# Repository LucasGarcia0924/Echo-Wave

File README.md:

# Echo-Wave

Banner 

## Descripción 
Dispositivo capaz de clonar señales RF de 433mhz, siendo controlado desde una App Movil

Proyecto final asignatura de Taller de Electrónica 2024-1

Universidad Nacional de Colombia
### Integrantes
* Lucas Garcia Alvarez
* Julian Gustin Moreno
* Kevin Castellanos Peña
* Santiago Navarro

## Introducción
El proyecto EchoWave se creó con la idea de facilitar la clonación de señales RF de controles remotos de distintos tipos, utilizando materiales de bajo costo para crear un dispositivo capaz de replicar y usar dichas señales. 

## La problemática
En la actualidad, el uso de controles remotos para dispositivos que emiten señales RF, como televisores, luces y otros equipos, se ha vuelto parte de las actividades cotidianas. Sin embargo, los usuarios enfrentan varios inconvenientes:

- Limitaciones de compatibilidad: Muchas veces los usuarios necesitan múltiples controles remotos, cada uno con una función específica, lo que resulta incómodo y poco eficiente.
- Falta de flexibilidad: Las tecnologías existentes no permiten la clonación o replicación de señales de RF de manera sencilla, lo que genera frustración entre los usuarios que requieren soluciones rápidas y accesibles.
- Riesgos de seguridad: Clonar señales RF sin los adecuados controles de seguridad puede conllevar riesgos, lo que hace que los usuarios se sientan inseguros al intentar utilizar tecnologías más flexibles.
Estas problemáticas crean la necesidad de desarrollar soluciones más accesibles y económicas que permitan clonar y utilizar señales RF de manera segura y eficiente, facilitando así las acciones cotidianas de los usuarios.

El proyecto EchoWave busca solucionar esta problemática mediante la creación de un dispositivo de bajo costo, flexible y eficiente, que permita la clonación y uso de señales de RF de manera segura, mejorando la experiencia del usuario y reduciendo la cantidad de controles remotos necesarios para interactuar con múltiples dispositivos.
## La solución planteada (los módulos usados)
La solución se diseña a partir de tecnologías simples, de fácil acceso y fabricación, enfocados en parte a que sea algo accesible para todo el mundo, por lo que a partir de esto y demás requisitos descritos a continuacion, se eligen los siguientes componentes:
- Chip ESP32
- Batería Recargable IN18650
- Modulo MHCD 42
- Transceptor HC-12
- Servomotor SG90
- Zumbador
- Case en Impresion 3D y Corte Laser
## El funcionamiento del proyecto desde el punto de vista del usuario

El EchoWave funciona como un control remoto universal, que mediante una aplicación, clona señales RF, como las de un control de televisor, controles para puertas de garaje o portones, y otros dispositivos similares  
Su uso consta tan solo de descargar la aplicación, clonar señales, cargar el dispositivo mediante el cable incluido y bloquear las señales con el pulsador en la parte superior del case.

## Recomendaciones y conclusiones
### Conclusiones:
En este proyecto se logró avanzar en le creación de una herramienta capaz de simplificar las tarjetas de acceso y controles a distancia de forma compacta, sin embargo, se enfocó el proyecto a las señales de radiofrecuencia, donde por medio de un transceptor recibe estas señales. Dentro del proyecto se utilizaron componentes con presupuesto reducido, confirmando que en el mercado se consiguen dispositivos de bajo precio y con las características que permiten manejar las diferentes señales y comunicaciones que se implementan aquí. Se plantea en un futuro implementarle la opción de usarse a bluetooth y hacer el uso de este desde una app del celular, dado que, quitando al tranceptor el cual es controlado desde la app diseñada por Slavko Zdravevski se implementó un grupo de pulsadores sencillos para que inicie su funcionamiento, por lo que lo ideal sería integrar todos estos comandos dentro de la app y así eliminar los pulsadores de la PCB.

### Recomendaciones para trabajos futuros:
Visualizamos que puede ser muy útil, buscar diferentes antecedentes de proyectos similares, componentes capaces de llevar a cabo la tarea y evaluar cuál lenguaje de programación ha de usarse.
Si se quiere hacer un trabajo en grupo, debe existir muy buena comunicación, de forma continua y clara entre todos, para que no se se tengan retrasos en el proceso, facilitando la corrección de errores y permitiendo un continuo ciclo de ideas y retroalimentación, para que el proyecto fluya correctamente.
Se deben tener en cuenta los posibles obstáculos que se pueden presentar durante el proceso, como puede ser el mal funcionamiento de un componente, o el fallo del código; para ello es necesario saber que otras alternativas existen, para corregir el error que se produzca al realizar el proyecto.

## WIKI
Si desea conocer más sobre este proyecto, podrá encontrar toda la documentación en la sección de [wiki](https://github.com/LucasGarcia0924/Echo-Wave/wiki), además, en este apartado en la parte superior se encuentran adjuntos todos los archivos relacionados con el proyecto.

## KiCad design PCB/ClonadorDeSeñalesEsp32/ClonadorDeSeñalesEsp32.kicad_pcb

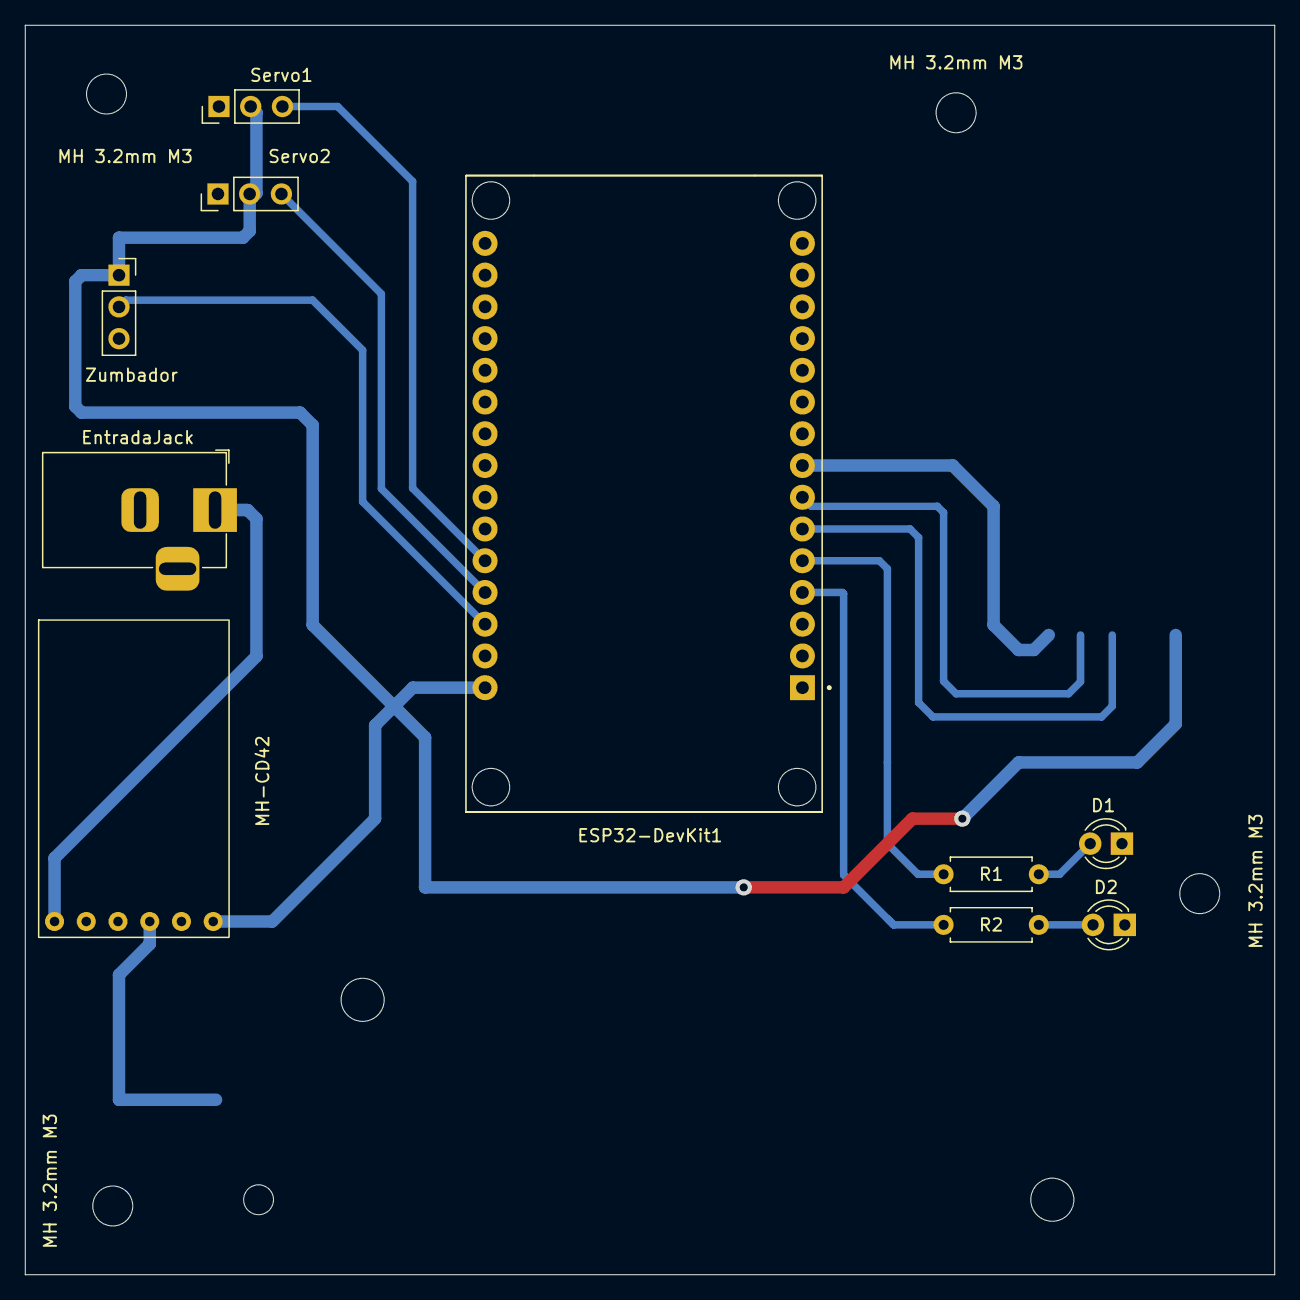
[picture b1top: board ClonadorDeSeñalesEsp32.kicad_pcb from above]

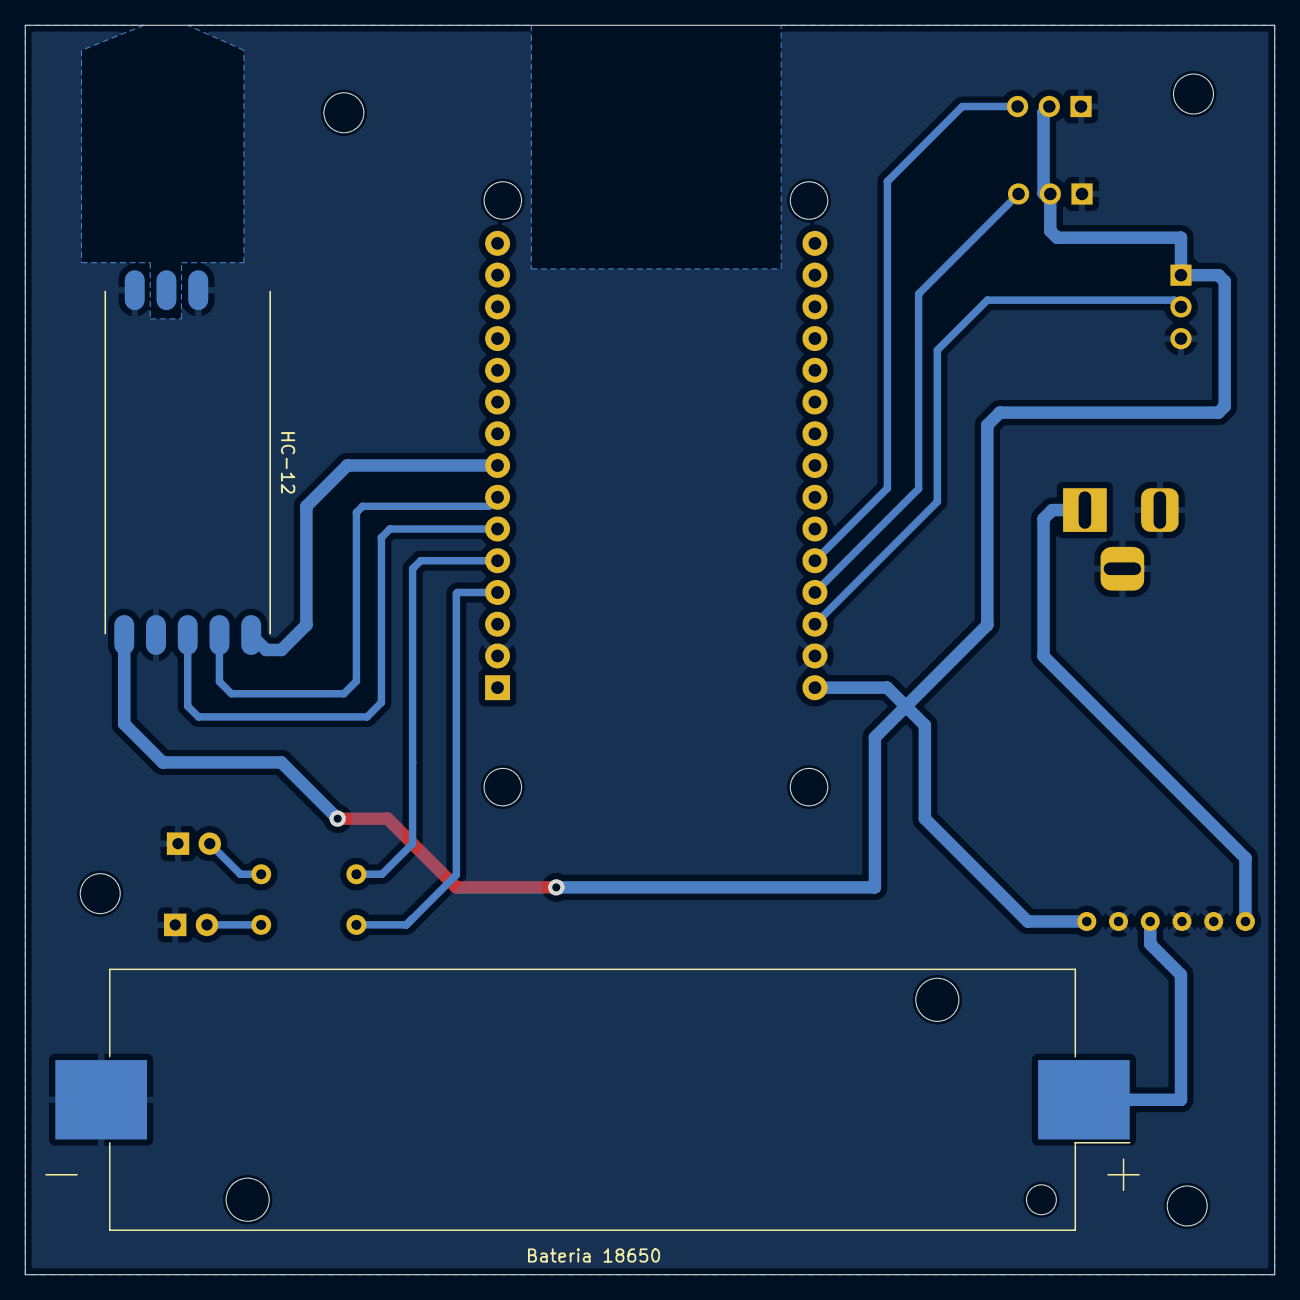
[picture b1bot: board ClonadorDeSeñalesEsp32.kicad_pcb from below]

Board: 2 copper layers, 100.0 x 100.0 mm, 16 parts (2 on the bottom side), 14 nets.

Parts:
Bateria 18650: Battery; BatteryHolder_Keystone_1042_1x18650
D1, D2: LED; LED_D3.0mm
ESP32-DevKit1: ESP32-DEVKIT-V1; MODULE_ESP32_DEVKIT_V1
EntradaJack: Entrada Jack; BarrelJack_Horizontal
HC-12: HC-12
MH 3.2mm M3: MH 3.2mm M3; MountingHole_3.2mm_M3
MH 3.2mm M3#2, MH 3.2mm M3#4: MH 32mm M3; MountingHole_3.2mm_M3
MH 3.2mm M3#3: MountingHole_3.2mm_M3
MH-CD42: MH-CD42; mh-cd42
R1, R2: R; R_Axial_DIN0207_L6.3mm_D2.5mm_P7.62mm_Horizontal
Servo1: Servo1; PinHeader_1x03_P2.54mm_Vertical
Servo2: Servo2; PinHeader_1x03_P2.54mm_Vertical
Zumbador: Zumbador; PinSocket_1x03_P2.54mm_Vertical

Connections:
+5V: ESP32-DevKit1.30 (VIN), HC-12.1 (VCC), MH-CD42.6 (OUT-5V), Servo1.2, Servo2.2, Zumbador.1
+BATT: Bateria 18650.1 (+), MH-CD42.4 (BAT)
/resistencia1: ESP32-DevKit1.5 (D4), R1.1
/resistencia2: ESP32-DevKit1.4 (D2), R2.1
/servo_1: ESP32-DevKit1.26 (D14), Servo1.3
/servo_2: ESP32-DevKit1.27 (D12), Servo2.3
/set_1: ESP32-DevKit1.8 (D5), HC-12.5 (SET)
/zumbador: ESP32-DevKit1.28 (D13), Zumbador.2
GND: Bateria 18650.2 (-), D1.1 (K), D2.1 (K), ESP32-DevKit1.2 (GND), ESP32-DevKit1.29 (GND), EntradaJack.2, EntradaJack.3, HC-12.2 (GND), HC-12.6 (GND@6), HC-12.8 (GND@8), MH-CD42.2 (GND), MH-CD42.3 (GND), MH-CD42.5 (GND), Servo1.1, Servo2.1, Zumbador.3
unnamed: D1.2 (A), R1.2
unnamed: D2.2 (A), R2.2
unnamed: ESP32-DevKit1.6 (RX2), HC-12.3 (RXD)
unnamed: ESP32-DevKit1.7 (TX2), HC-12.4 (TXD)
VDC: EntradaJack.1, MH-CD42.1 (VIN)

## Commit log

2024-08-28 Guardado de PCB en la Nube
2024-08-28 Cambio de nombre
2024-08-28 Delete PCB/ClonadorDeSeñalesEsp32/GERBER.rar
    Se borra el Gerber desactualizado
2024-08-28 Fin de la PCB
2024-08-28 Fotos del diseño electrónico
2024-08-28 Actualización de fotos
2024-08-28 Fin de la PCB
    PCB después de revisión del profesor
2024-08-28 Update README.md
    Complemento Readme 1
2024-08-28 README.md
2024-08-28 gerber final
2024-08-30 diagrama final
2024-09-25 Añadir imagenes
2024-09-25 imagenes
2024-09-25 actualizacion fotos
2024-09-25 errase
2024-09-25 fotos
2024-09-25 ardhivos
2024-09-25 Update Evidencias
2024-09-25 organizar carpetas
